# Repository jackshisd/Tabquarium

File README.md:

# Tabquarium - ESP32-C3 Aquarium Game

Tabquarium is an ESP-IDF aquarium game for an SSD1306 128x64 OLED with fish collecting, decorations, blindbox rewards, persistent save data, weather effects, and sleep-aware simulation.

## Current Platform

- Target MCU: ESP32-C3
- Framework: ESP-IDF v5.4.x
- Display: SSD1306 (I2C, monochrome 128x64)

## Hardware Wiring (ESP32-C3)

### OLED (SSD1306, I2C)

- VCC -> 3.3V
- GND -> GND
- SDA -> GPIO 5
- SCL -> GPIO 6

### Buttons

- Mode button -> GPIO 21
- Action button -> GPIO 20
- Tabs/Reward button -> GPIO 7

### LED

- Hunger/alert LED -> GPIO 10

## Game Controls

- `Mode`: cycles main screens (Blindbox -> Aquarium -> Fish -> Decorations)
- `Action` on Blindbox: shake/open rewards
- `Action` in Aquarium: feed fish (drops random top-spawn food pieces)
- `Tabs` on Blindbox: earn +1 tab with cooldown
- Clock set mode:
  - Enter/exit with mode+action hold combo
  - Action adjusts hour
  - Mode adjusts minute

## Core Features

- Blindbox rewards with 80% fish / 20% decoration odds
- Persistent fish, decorations, tabs, clock, and tank hunger state via NVS
- Persistent hourly weather seed via NVS
- Decor ownership tracking separate from active visible decor slots
- Tank-wide hunger system (single tank timer instead of per-fish hunger)
- Starvation system:
  - First random fish death when hunger reaches zero
  - Then one random fish death every 24h while unfed
- Wake/offline progression using saved unix timestamps
- Clock restore on boot from saved unix time
- Startup overlays:
  - Save corruption warning
  - Offline death summary
  - Dismissed by button press
- Save schema recovery:
  - Legacy fish blob migration path before corruption fallback
- Fish behaviors:
  - Committed food targeting so a fish chases its chosen pellet instead of constantly retargeting
  - Some fish intentionally prefer the second- or third-closest pellet when multiple food pieces exist
  - Species movement variants (including snail/crab behavior)
  - Nighttime sleep behavior with floating sleep `Z` particles
- Food system:
  - 2-3 food pieces per feed action
  - Top spawn, lifetime/consume timers, and touch/consume logic
  - Pellets keep falling even when untouched and expire after 10 seconds
- Weather system:
  - Hour-long weather seed with chunked rain and sun-ray windows
  - Rain occupies 15% of seeded time
  - Sun rays occupy 30% of non-rain seeded time
  - Rain suppresses sun rays while active
  - Thunderstorms can occur during rain and flash the composed frame
- UI/sleep behavior:
  - Input lockout after wake to avoid accidental presses
  - Clock-set screen blocks idle sleep
  - Changing the clock invalidates the current weather seed so a new hour schedule is generated
- LED behavior:
  - Blinks when tank reaches half-hunger threshold
  - 2-second solid pulse when a tab reward is earned
- Rendering polish:
  - Multiple fish and decor sprite spacing/alignment tweaks
  - Dotted sunbeams that keep a stable origin while active
  - Rain droplets that become expanding surface ripples
  - Clock-set display position adjustments
  - "Tabquarium" branding text in UI
  - Decor label update: "Oyster Pearl"

## Build and Flash

### Prerequisites

- ESP-IDF installed and exported in shell
- `idf.py` available

### Build

```bash
idf.py build
```

### Flash

```bash
idf.py flash
```

### Monitor

```bash
idf.py monitor
```

### Full Cycle

```bash
idf.py build flash monitor
```

## Project Layout

```text
.
├── CMakeLists.txt
├── sdkconfig
├── main/
│   ├── aquarium.c
│   ├── aquarium.h
│   ├── display.c
│   ├── gifts.c
│   ├── input.c
│   └── ui.c
└── .github/
    └── copilot-instructions.md
```

## Notes

- Frame cadence targets ~60 FPS (`vTaskDelay(17ms)` cadence in UI loop).
- Current dev toggles for weather testing live near the top of [`main/aquarium.c`](main/aquarium.c):
  - `always_raining`
  - `always_thunder`

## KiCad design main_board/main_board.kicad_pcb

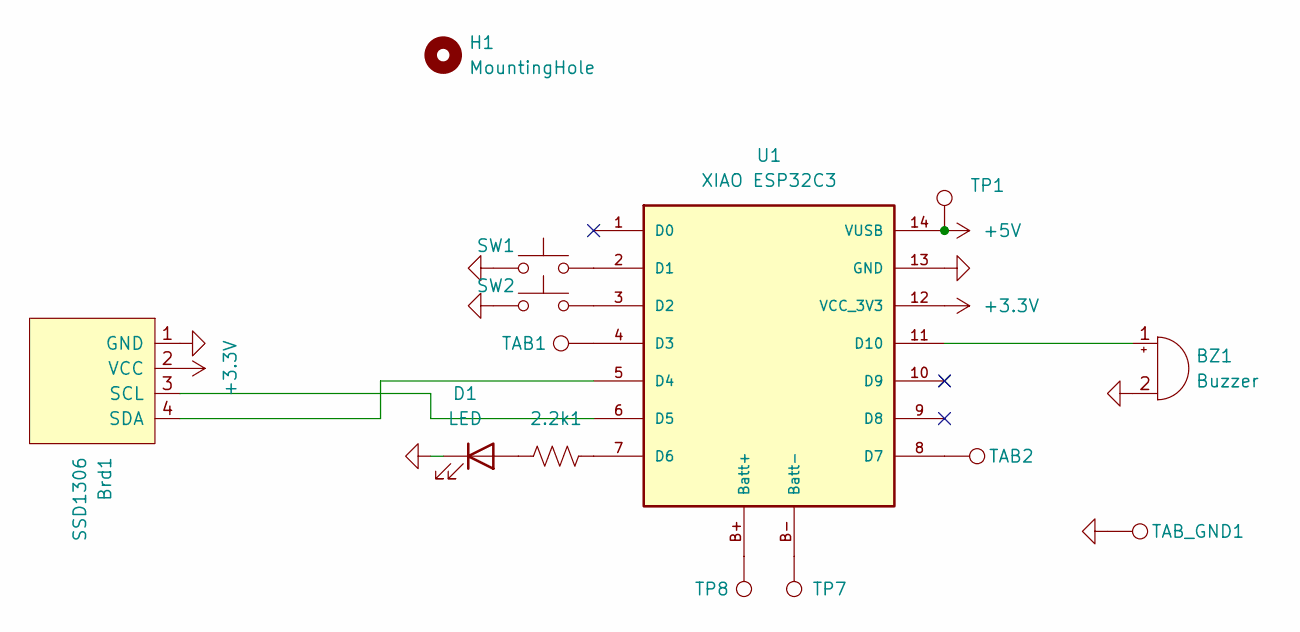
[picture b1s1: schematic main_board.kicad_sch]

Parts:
2.2k1: R_US; R_1206_3216Metric_Pad1.30x1.75mm_HandSolder
BZ1: Buzzer; XDCR_SMT-0440-T-R
Brd1: SSD1306; 128x64OLED
D1: LED; LED_1206_3216Metric_Pad1.42x1.75mm_HandSolder
H1: MountingHole; MountingHole_2mm
SW1, SW2: SW_Push; SW_SPST_TL3342
TAB1, TAB2: TestPoint; PinHeader_1x01_P2.54mm_Vertical
TAB_GND1: TestPoint; PinHeader_1x01_P2.54mm_Vertical
TP1, TP7, TP8: TestPoint; TestPoint_Pad_1.5x1.5mm
U1: XIAO ESP32C3; xiao_esp32c3

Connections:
+3.3V: Brd1.2 (VCC), U1.12 (VCC_3V3)
+5V: TP1.1, U1.14 (VUSB)
GND: BZ1.2 (-), Brd1.1 (GND), D1.1 (K), SW1.1, SW2.1, TAB_GND1.1, U1.13 (GND)
unnamed: BZ1.1 (+), U1.11 (D10)
unnamed: Brd1.3 (SCL), U1.6 (D5)
unnamed: Brd1.4 (SDA), U1.5 (D4)
unnamed: 2.2k1.1, D1.2 (A)
unnamed: TP8.1, U1.B+ (Batt+)
unnamed: TP7.1, U1.B- (Batt-)
unnamed: SW1.2, U1.2 (D1)
unnamed: SW2.2, U1.3 (D2)
unnamed: TAB1.1, U1.4 (D3)
unnamed: 2.2k1.2, U1.7 (D6)
unnamed: TAB2.1, U1.8 (D7)

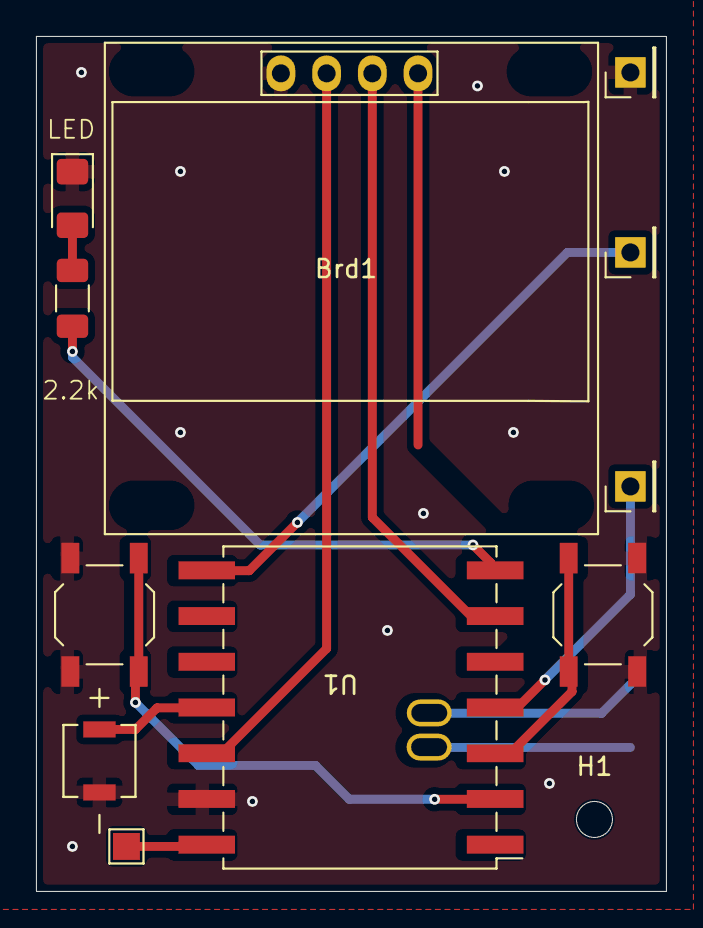
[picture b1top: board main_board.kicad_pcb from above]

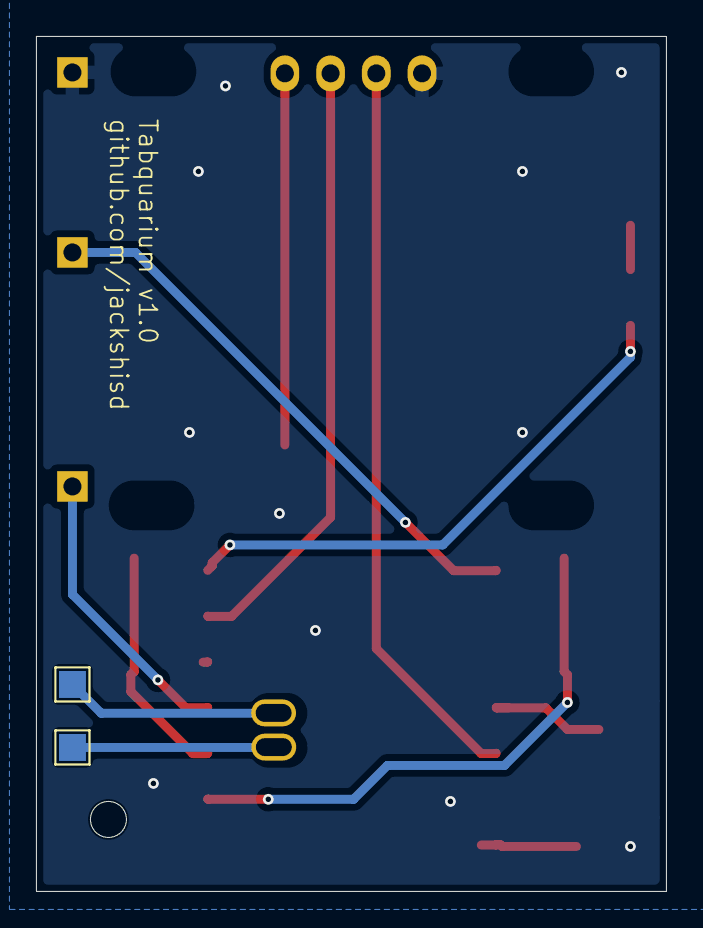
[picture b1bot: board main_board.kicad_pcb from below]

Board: 2 copper layers, 35.0 x 47.5 mm, 14 parts (2 on the bottom side), 14 nets.

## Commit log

2026-04-08 Initial project import
2026-04-09 Add save migration, startup overlays, clock/sleep UX, reward LED pulse, and gameplay polish
    - add save schema versioning and legacy fish-blob migration before corruption fallback
    - persist and surface startup overlays (corruption/offline events) with dismiss-on-input behavior
    - keep clock-set screen awake and adjust clock-set rendering position
    - trigger a 2-second LED pulse when tabs are earned while preserving hunger alert behavior
    - speed up bubble rise animation and rename decor label to 'Oyster Pearl'
    - document current ESP32-C3 wiring, controls, features, and build flow in README
2026-04-11 Add weather effects and aquarium behavior updates
2026-04-12 included hardware schematics and layout
2026-04-21 I updated the case in the hardware folder
